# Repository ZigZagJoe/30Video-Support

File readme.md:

This is the support repository for the 30Video series of video cards, by zigzagjoe.

https://68kmla.org/bb/index.php?threads/fs-30video-gs-internal-grayscale-for-se-30.47879/
https://68kmla.org/bb/index.php?threads/30video-new-video-board-for-se-30-iisi-more.47649/

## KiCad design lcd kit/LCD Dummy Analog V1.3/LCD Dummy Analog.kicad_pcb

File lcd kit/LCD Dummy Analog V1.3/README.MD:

# LCD Kit "Analog" Board.
This board is used to replace the original analog board.

The contents of this folder are subject to the CERN OHL License, the contents of which follow.

Please do not commercially distribute these boards without first contacting me. Selling extra boards in a noncommercial fashion not for profit is fine. 

# CERN Open Hardware Licence Version 2 - Strongly Reciprocal

Preamble

CERN has developed this licence to promote collaboration among
hardware designers and to provide a legal tool which supports the
freedom to use, study, modify, share and distribute hardware designs
and products based on those designs. Version 2 of the CERN Open
Hardware Licence comes in three variants: CERN-OHL-P (permissive); and
two reciprocal licences: CERN-OHL-W (weakly reciprocal) and this
licence, CERN-OHL-S (strongly reciprocal).

The CERN-OHL-S is copyright CERN 2020. Anyone is welcome to use it, in
unmodified form only.

Use of this Licence does not imply any endorsement by CERN of any
Licensor or their designs nor does it imply any involvement by CERN in
their development.

1 Definitions

  1.1 'Licence' means this CERN-OHL-S.

  1.2 'Compatible Licence' means

       a) any earlier version of the CERN Open Hardware licence, or

       b) any version of the CERN-OHL-S, or

       c) any licence which permits You to treat the Source to which
          it applies as licensed under CERN-OHL-S provided that on
          Conveyance of any such Source, or any associated Product You
          treat the Source in question as being licensed under
          CERN-OHL-S.

  1.3 'Source' means information such as design materials or digital
      code which can be applied to Make or test a Product or to
      prepare a Product for use, Conveyance or sale, regardless of its
      medium or how it is expressed. It may include Notices.

  1.4 'Covered Source' means Source that is explicitly made available
      under this Licence.

  1.5 'Product' means any device, component, work or physical object,
      whether in finished or intermediate form, arising from the use,
      application or processing of Covered Source.

  1.6 'Make' means to create or configure something, whether by
      manufacture, assembly, compiling, loading or applying Covered
      Source or another Product or otherwise.

  1.7 'Available Component' means any part, sub-assembly, library or
      code which:

       a) is licensed to You as Complete Source under a Compatible
          Licence; or

       b) is available, at the time a Product or the Source containing
          it is first Conveyed, to You and any other prospective
          licensees

            i) as a physical part with sufficient rights and
               information (including any configuration and
               programming files and information about its
               characteristics and interfaces) to enable it either to
               be Made itself, or to be sourced and used to Make the
               Product; or
           ii) as part of the normal distribution of a tool used to
               design or Make the Product.

  1.8 'Complete Source' means the set of all Source necessary to Make
      a Product, in the preferred form for making modifications,
      including necessary installation and interfacing information
      both for the Product, and for any included Available Components.
      If the format is proprietary, it must also be made available in
      a format (if the proprietary tool can create it) which is
      viewable with a tool available to potential licensees and
      licensed under a licence approved by the Free Software
      Foundation or the Open Source Initiative. Complete Source need
      not include the Source of any Available Component, provided that
      You include in the Complete Source sufficient information to
      enable a recipient to Make or source and use the Available
      Component to Make the Product.

  1.9 'Source Location' means a location where a Licensor has placed
      Covered Source, and which that Licensor reasonably believes will
      remain easily accessible for at least three years for anyone to
      obtain a digital copy.

 1.10 'Notice' means copyright, acknowledgement and trademark notices,
      Source Location references, modification notices (subsection
      3.3(b)) and all notices that refer to this Licence and to the
      disclaimer of warranties that are included in the Covered
      Source.

 1.11 'Licensee' or 'You' means any person exercising rights under
      this Licence.

 1.12 'Licensor' means a natural or legal person who creates or
      modifies Covered Source. A person may be a Licensee and a
      Licensor at the same time.

 1.13 'Convey' means to communicate to the public or distribute.

2 Applicability

  2.1 This Licence governs the use, copying, modification, Conveying
      of Covered Source and Products, and the Making of Products. By
      exercising any right granted under this Licence, You irrevocably
      accept these terms and conditions.

  2.2 This Licence is granted by the Licensor directly to You, and
      shall apply worldwide and without limitation in time.

  2.3 You shall not attempt to restrict by contract or otherwise the
      rights granted under this Licence to other Licensees.

  2.4 This Licence is not intended to restrict fair use, fair dealing,
      or any other similar right.

3 Copying, Modifying and Conveying Covered Source

  3.1 You may copy and Convey verbatim copies of Covered Source, in
      any medium, provided You retain all Notices.

  3.2 You may modify Covered Source, other than Notices, provided that
      You irrevocably undertake to make that modified Covered Source
      available from a Source Location should You Convey a Product in
      circumstances where the recipient does not otherwise receive a
      copy of the modified Covered Source. In each case subsection 3.3
      shall apply.

      You may only delete Notices if they are no longer applicable to
      the corresponding Covered Source as modified by You and You may
      add additional Notices applicable to Your modifications.
      Including Covered Source in a larger work is modifying the
      Covered Source, and the larger work becomes modified Covered
      Source.

  3.3 You may Convey modified Covered Source (with the effect that You
      shall also become a Licensor) provided that You:

       a) retain Notices as required in subsection 3.2;

       b) add a Notice to the modified Covered Source stating that You
          have modified it, with the date and brief description of how
          You have modified it;

       c) add a Source Location Notice for the modified Covered Source
          if You Convey in circumstances where the recipient does not
          otherwise receive a copy of the modified Covered Source; and

       d) license the modified Covered Source under the terms and
          conditions of this Licence (or, as set out in subsection
          8.3, a later version, if permitted by the licence of the
          original Covered Source). Such modified Covered Source must
          be licensed as a whole, but excluding Available Components
          contained in it, which remain licensed under their own
          applicable licences.

4 Making and Conveying Products

You may Make Products, and/or Convey them, provided that You either
provide each recipient with a copy of the Complete Source or ensure
that each recipient is notified of the Source Location of the Complete
Source. That Complete Source is Covered Source, and You must
accordingly satisfy Your obligations set out in subsection 3.3. If
specified in a Notice, the Product must visibly and securely display
the Source Location on it or its packaging or documentation in the
manner specified in that Notice.

5 Research and Development

You may Convey Covered Source, modified Covered Source or Products to
a legal entity carrying out development, testing or quality assurance
work on Your behalf provided that the work is performed on terms which
prevent the entity from both using the Source or Products for its own
internal purposes and Conveying the Source or Products or any
modifications to them to any person other than You. Any modifications
made by the entity shall be deemed to be made by You pursuant to
subsection 3.2.

6 DISCLAIMER AND LIABILITY

  6.1 DISCLAIMER OF WARRANTY -- The Covered Source and any Products
      are provided 'as is' and any express or implied warranties,
      including, but not limited to, implied warranties of
      merchantability, of satisfactory quality, non-infringement of
      third party rights, and fitness for a particular purpose or use
      are disclaimed in respect of any Source or Product to the
      maximum extent permitted by law. The Licensor makes no
      representation that any Source or Product does not or will not
      infringe any patent, copyright, trade secret or other
      proprietary right. The entire risk as to the use, quality, and
      performance of any Source or Product shall be with You and not
      the Licensor. This disclaimer of warranty is an essential part
      of this Licence and a condition for the grant of any rights
      granted under this Licence.

  6.2 EXCLUSION AND LIMITATION OF LIABILITY -- The Licensor shall, to
      the maximum extent permitted by law, have no liability for
      direct, indirect, special, incidental, consequential, exemplary,
      punitive or other damages of any character including, without
      limitation, procurement of substitute goods or services, loss of
      use, data or profits, or business interruption, however caused
      and on any theory of contract, warranty, tort (including
      negligence), product liability or otherwise, arising in any way
      in relation to the Covered Source, modified Covered Source
      and/or the Making or Conveyance of a Product, even if advised of
      the possibility of such damages, and You shall hold the
      Licensor(s) free and harmless from any liability, costs,
      damages, fees and expenses, including claims by third parties,
      in relation to such use.

7 Patents

  7.1 Subject to the terms and conditions of this Licence, each
      Licensor hereby grants to You a perpetual, worldwide,
      non-exclusive, no-charge, royalty-free, irrevocable (except as
      stated in subsections 7.2 and 8.4) patent licence to Make, have
      Made, use, offer to sell, sell, import, and otherwise transfer
      the Covered Source and Products, where such licence applies only
      to those patent claims licensable by such Licensor that are
      necessarily infringed by exercising rights under the Covered
      Source as Conveyed by that Licensor.

  7.2 If You institute patent litigation against any entity (including
      a cross-claim or counterclaim in a lawsuit) alleging that the
      Covered Source or a Product constitutes direct or contributory
      patent infringement, or You seek any declaration that a patent
      licensed to You under this Licence is invalid or unenforceable
      then any rights granted to You under this Licence shall
      terminate as of the date such process is initiated.

8 General

  8.1 If any provisions of this Licence are or subsequently become
      invalid or unenforceable for any reason, the remaining
      provisions shall remain effective.

  8.2 You shall not use any of the name (including acronyms and
      abbreviations), image, or logo by which the Licensor or CERN is
      known, except where needed to comply with section 3, or where
      the use is otherwise allowed by law. Any such permitted use
      shall be factual and shall not be made so as to suggest any kind
      of endorsement or implication of involvement by the Licensor or
      its personnel.

  8.3 CERN may publish updated versions and variants of this Licence
      which it considers to be in the spirit of this version, but may
      differ in detail to address new problems or concerns. New
      versions will be published with a unique version number and a
      variant identifier specifying the variant. If the Licensor has
      specified that a given variant applies to the Covered Source
      without specifying a version, You may treat that Covered Source
      as being released under any version of the CERN-OHL with that
      variant. If no variant is specified, the Covered Source shall be
      treated as being released under CERN-OHL-S. The Licensor may
      also specify that the Covered Source is subject to a specific
      version of the CERN-OHL or any later version in which case You
      may apply this or any later version of CERN-OHL with the same
      variant identifier published by CERN.

  8.4 This Licence shall terminate with immediate effect if You fail
      to comply with any of its terms and conditions.

  8.5 However, if You cease all breaches of this Licence, then Your
      Licence from any Licensor is reinstated unless such Licensor has
      terminated this Licence by giving You, while You remain in
      breach, a notice specifying the breach and requiring You to cure
      it within 30 days, and You have failed to come into compliance
      in all material respects by the end of the 30 day period. Should
      You repeat the breach after receipt of a cure notice and
      subsequent reinstatement, this Licence will terminate
      immediately and permanently. Section 6 shall continue to apply
      after any termination.

  8.6 This Licence shall not be enforceable except by a Licensor
      acting as such, and third party beneficiary rights are
      specifically excluded.

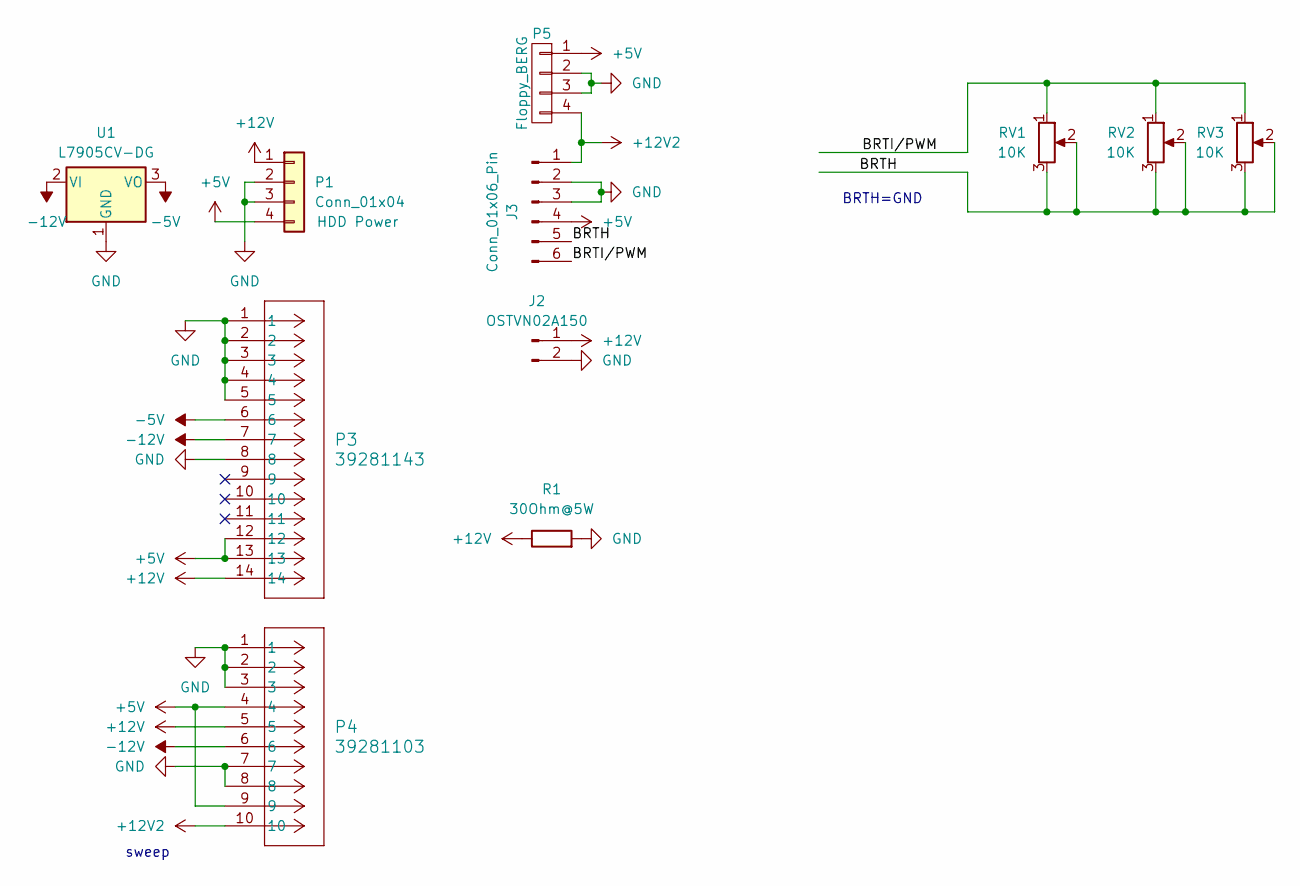
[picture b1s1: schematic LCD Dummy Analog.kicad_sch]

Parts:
J2: OSTVN02A150; PinHeader_1x02_P2.54mm_Vertical
J3: Conn_01x06_Pin; JST_XH_B6B-XH-A_1x06_P2.50mm_Vertical
P1: Conn_01x04; TE_MATE-N-LOK_350211-1_1x04_P5.08mm_Vertical
P3: 39281143; SE30AB_CON_39281143
P4: 39281103; SE30AB_CON_39281103
P5: Floppy_BERG; floppy-berg; digikey S9490-ND
R1: 30Ohm@5W; R_Axial_Power_L25.0mm_W6.4mm_P30.48mm
RV1, RV2, RV3: 10K; Potentiometer_Piher_T-16H_Single_Horizontal
U1: L7905CV-DG; TO-220-3_Horizontal_TabDown

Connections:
+5V: J3.4, P1.4, P3.12, P3.13, P4.4, P4.9, P5.1
+12V: J2.1, P1.1, P3.14, P4.5, R1.1
+12V2: J3.1, P4.10, P5.4
-5V: P3.6, U1.3 (VO)
-12V: P3.7, P4.6, U1.2 (VI)
/BRTH: J3.5, RV1.2, RV1.3, RV2.2, RV2.3, RV3.2, RV3.3
/BRTI/PWM: J3.6, RV1.1, RV2.1, RV3.1
GND: J2.2, J3.2, J3.3, P1.2, P1.3, P3.1, P3.2, P3.3, P3.4, P3.5, P3.8, P4.1, P4.2, P4.3, P4.7, P4.8, P5.2, P5.3, R1.2, U1.1 (GND)

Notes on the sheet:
sweep
BRTH=GND

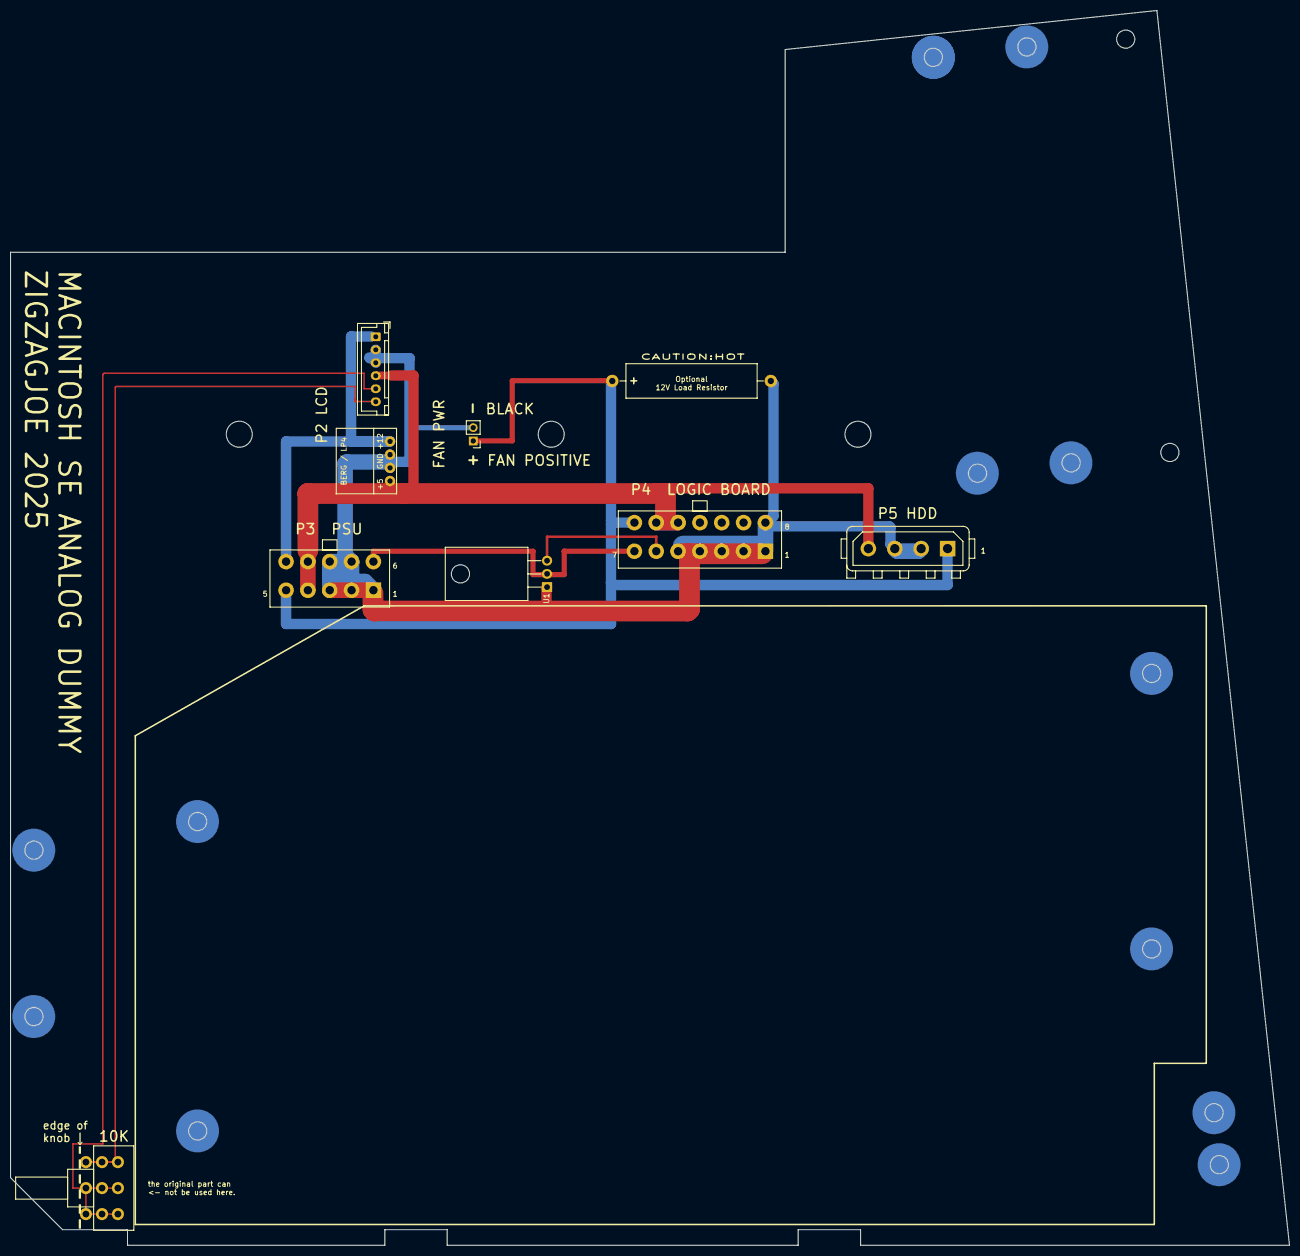
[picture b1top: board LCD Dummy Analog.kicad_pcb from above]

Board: 2 copper layers, 246.0 x 237.5 mm, 11 parts (0 on the bottom side), 8 nets.

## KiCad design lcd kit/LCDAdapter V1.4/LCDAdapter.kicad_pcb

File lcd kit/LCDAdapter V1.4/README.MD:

# LCD Kit "Adapter" Board
This board is used to adapt the 30Video's LCD interface to the NL6448BC26-26F.

The contents of this folder are subject to the CERN OHL License, the contents of which follow.

Please do not commercially distribute these boards without first contacting me. Selling extra boards in a noncommercial fashion not for profit is fine. 

# CERN Open Hardware Licence Version 2 - Strongly Reciprocal

Preamble

CERN has developed this licence to promote collaboration among
hardware designers and to provide a legal tool which supports the
freedom to use, study, modify, share and distribute hardware designs
and products based on those designs. Version 2 of the CERN Open
Hardware Licence comes in three variants: CERN-OHL-P (permissive); and
two reciprocal licences: CERN-OHL-W (weakly reciprocal) and this
licence, CERN-OHL-S (strongly reciprocal).

The CERN-OHL-S is copyright CERN 2020. Anyone is welcome to use it, in
unmodified form only.

Use of this Licence does not imply any endorsement by CERN of any
Licensor or their designs nor does it imply any involvement by CERN in
their development.

1 Definitions

  1.1 'Licence' means this CERN-OHL-S.

  1.2 'Compatible Licence' means

       a) any earlier version of the CERN Open Hardware licence, or

       b) any version of the CERN-OHL-S, or

       c) any licence which permits You to treat the Source to which
          it applies as licensed under CERN-OHL-S provided that on
          Conveyance of any such Source, or any associated Product You
          treat the Source in question as being licensed under
          CERN-OHL-S.

  1.3 'Source' means information such as design materials or digital
      code which can be applied to Make or test a Product or to
      prepare a Product for use, Conveyance or sale, regardless of its
      medium or how it is expressed. It may include Notices.

  1.4 'Covered Source' means Source that is explicitly made available
      under this Licence.

  1.5 'Product' means any device, component, work or physical object,
      whether in finished or intermediate form, arising from the use,
      application or processing of Covered Source.

  1.6 'Make' means to create or configure something, whether by
      manufacture, assembly, compiling, loading or applying Covered
      Source or another Product or otherwise.

  1.7 'Available Component' means any part, sub-assembly, library or
      code which:

       a) is licensed to You as Complete Source under a Compatible
          Licence; or

       b) is available, at the time a Product or the Source containing
          it is first Conveyed, to You and any other prospective
          licensees

            i) as a physical part with sufficient rights and
               information (including any configuration and
               programming files and information about its
               characteristics and interfaces) to enable it either to
               be Made itself, or to be sourced and used to Make the
               Product; or
           ii) as part of the normal distribution of a tool used to
               design or Make the Product.

  1.8 'Complete Source' means the set of all Source necessary to Make
      a Product, in the preferred form for making modifications,
      including necessary installation and interfacing information
      both for the Product, and for any included Available Components.
      If the format is proprietary, it must also be made available in
      a format (if the proprietary tool can create it) which is
      viewable with a tool available to potential licensees and
      licensed under a licence approved by the Free Software
      Foundation or the Open Source Initiative. Complete Source need
      not include the Source of any Available Component, provided that
      You include in the Complete Source sufficient information to
      enable a recipient to Make or source and use the Available
      Component to Make the Product.

  1.9 'Source Location' means a location where a Licensor has placed
      Covered Source, and which that Licensor reasonably believes will
      remain easily accessible for at least three years for anyone to
      obtain a digital copy.

 1.10 'Notice' means copyright, acknowledgement and trademark notices,
      Source Location references, modification notices (subsection
      3.3(b)) and all notices that refer to this Licence and to the
      disclaimer of warranties that are included in the Covered
      Source.

 1.11 'Licensee' or 'You' means any person exercising rights under
      this Licence.

 1.12 'Licensor' means a natural or legal person who creates or
      modifies Covered Source. A person may be a Licensee and a
      Licensor at the same time.

 1.13 'Convey' means to communicate to the public or distribute.

2 Applicability

  2.1 This Licence governs the use, copying, modification, Conveying
      of Covered Source and Products, and the Making of Products. By
      exercising any right granted under this Licence, You irrevocably
      accept these terms and conditions.

  2.2 This Licence is granted by the Licensor directly to You, and
      shall apply worldwide and without limitation in time.

  2.3 You shall not attempt to restrict by contract or otherwise the
      rights granted under this Licence to other Licensees.

  2.4 This Licence is not intended to restrict fair use, fair dealing,
      or any other similar right.

3 Copying, Modifying and Conveying Covered Source

  3.1 You may copy and Convey verbatim copies of Covered Source, in
      any medium, provided You retain all Notices.

  3.2 You may modify Covered Source, other than Notices, provided that
      You irrevocably undertake to make that modified Covered Source
      available from a Source Location should You Convey a Product in
      circumstances where the recipient does not otherwise receive a
      copy of the modified Covered Source. In each case subsection 3.3
      shall apply.

      You may only delete Notices if they are no longer applicable to
      the corresponding Covered Source as modified by You and You may
      add additional Notices applicable to Your modifications.
      Including Covered Source in a larger work is modifying the
      Covered Source, and the larger work becomes modified Covered
      Source.

  3.3 You may Convey modified Covered Source (with the effect that You
      shall also become a Licensor) provided that You:

       a) retain Notices as required in subsection 3.2;

       b) add a Notice to the modified Covered Source stating that You
          have modified it, with the date and brief description of how
          You have modified it;

       c) add a Source Location Notice for the modified Covered Source
          if You Convey in circumstances where the recipient does not
          otherwise receive a copy of the modified Covered Source; and

       d) license the modified Covered Source under the terms and
          conditions of this Licence (or, as set out in subsection
          8.3, a later version, if permitted by the licence of the
          original Covered Source). Such modified Covered Source must
          be licensed as a whole, but excluding Available Components
          contained in it, which remain licensed under their own
          applicable licences.

4 Making and Conveying Products

You may Make Products, and/or Convey them, provided that You either
provide each recipient with a copy of the Complete Source or ensure
that each recipient is notified of the Source Location of the Complete
Source. That Complete Source is Covered Source, and You must
accordingly satisfy Your obligations set out in subsection 3.3. If
specified in a Notice, the Product must visibly and securely display
the Source Location on it or its packaging or documentation in the
manner specified in that Notice.

5 Research and Development

You may Convey Covered Source, modified Covered Source or Products to
a legal entity carrying out development, testing or quality assurance
work on Your behalf provided that the work is performed on terms which
prevent the entity from both using the Source or Products for its own
internal purposes and Conveying the Source or Products or any
modifications to them to any person other than You. Any modifications
made by the entity shall be deemed to be made by You pursuant to
subsection 3.2.

6 DISCLAIMER AND LIABILITY

  6.1 DISCLAIMER OF WARRANTY -- The Covered Source and any Products
      are provided 'as is' and any express or implied warranties,
      including, but not limited to, implied warranties of
      merchantability, of satisfactory quality, non-infringement of
      third party rights, and fitness for a particular purpose or use
      are disclaimed in respect of any Source or Product to the
      maximum extent permitted by law. The Licensor makes no
      representation that any Source or Product does not or will not
      infringe any patent, copyright, trade secret or other
      proprietary right. The entire risk as to the use, quality, and
      performance of any Source or Product shall be with You and not
      the Licensor. This disclaimer of warranty is an essential part
      of this Licence and a condition for the grant of any rights
      granted under this Licence.

  6.2 EXCLUSION AND LIMITATION OF LIABILITY -- The Licensor shall, to
      the maximum extent permitted by law, have no liability for
      direct, indirect, special, incidental, consequential, exemplary,
      punitive or other damages of any character including, without
      limitation, procurement of substitute goods or services, loss of
      use, data or profits, or business interruption, however caused
      and on any theory of contract, warranty, tort (including
      negligence), product liability or otherwise, arising in any way
      in relation to the Covered Source, modified Covered Source
      and/or the Making or Conveyance of a Product, even if advised of
      the possibility of such damages, and You shall hold the
      Licensor(s) free and harmless from any liability, costs,
      damages, fees and expenses, including claims by third parties,
      in relation to such use.

7 Patents

  7.1 Subject to the terms and conditions of this Licence, each
      Licensor hereby grants to You a perpetual, worldwide,
      non-exclusive, no-charge, royalty-free, irrevocable (except as
      stated in subsections 7.2 and 8.4) patent licence to Make, have
      Made, use, offer to sell, sell, import, and otherwise transfer
      the Covered Source and Products, where such licence applies only
      to those patent claims licensable by such Licensor that are
      necessarily infringed by exercising rights under the Covered
      Source as Conveyed by that Licensor.

  7.2 If You institute patent litigation against any entity (including
      a cross-claim or counterclaim in a lawsuit) alleging that the
      Covered Source or a Product constitutes direct or contributory
      patent infringement, or You seek any declaration that a patent
      licensed to You under this Licence is invalid or unenforceable
      then any rights granted to You under this Licence shall
      terminate as of the date such process is initiated.

8 General

  8.1 If any provisions of this Licence are or subsequently become
      invalid or unenforceable for any reason, the remaining
      provisions shall remain effective.

  8.2 You shall not use any of the name (including acronyms and
      abbreviations), image, or logo by which the Licensor or CERN is
      known, except where needed to comply with section 3, or where
      the use is otherwise allowed by law. Any such permitted use
      shall be factual and shall not be made so as to suggest any kind
      of endorsement or implication of involvement by the Licensor or
      its personnel.

  8.3 CERN may publish updated versions and variants of this Licence
      which it considers to be in the spirit of this version, but may
      differ in detail to address new problems or concerns. New
      versions will be published with a unique version number and a
      variant identifier specifying the variant. If the Licensor has
      specified that a given variant applies to the Covered Source
      without specifying a version, You may treat that Covered Source
      as being released under any version of the CERN-OHL with that
      variant. If no variant is specified, the Covered Source shall be
      treated as being released under CERN-OHL-S. The Licensor may
      also specify that the Covered Source is subject to a specific
      version of the CERN-OHL or any later version in which case You
      may apply this or any later version of CERN-OHL with the same
      variant identifier published by CERN.

  8.4 This Licence shall terminate with immediate effect if You fail
      to comply with any of its terms and conditions.

  8.5 However, if You cease all breaches of this Licence, then Your
      Licence from any Licensor is reinstated unless such Licensor has
      terminated this Licence by giving You, while You remain in
      breach, a notice specifying the breach and requiring You to cure
      it within 30 days, and You have failed to come into compliance
      in all material respects by the end of the 30 day period. Should
      You repeat the breach after receipt of a cure notice and
      subsequent reinstatement, this Licence will terminate
      immediately and permanently. Section 6 shall continue to apply
      after any termination.

  8.6 This Licence shall not be enforceable except by a Licensor
      acting as such, and third party beneficiary rights are
      specifically excluded.

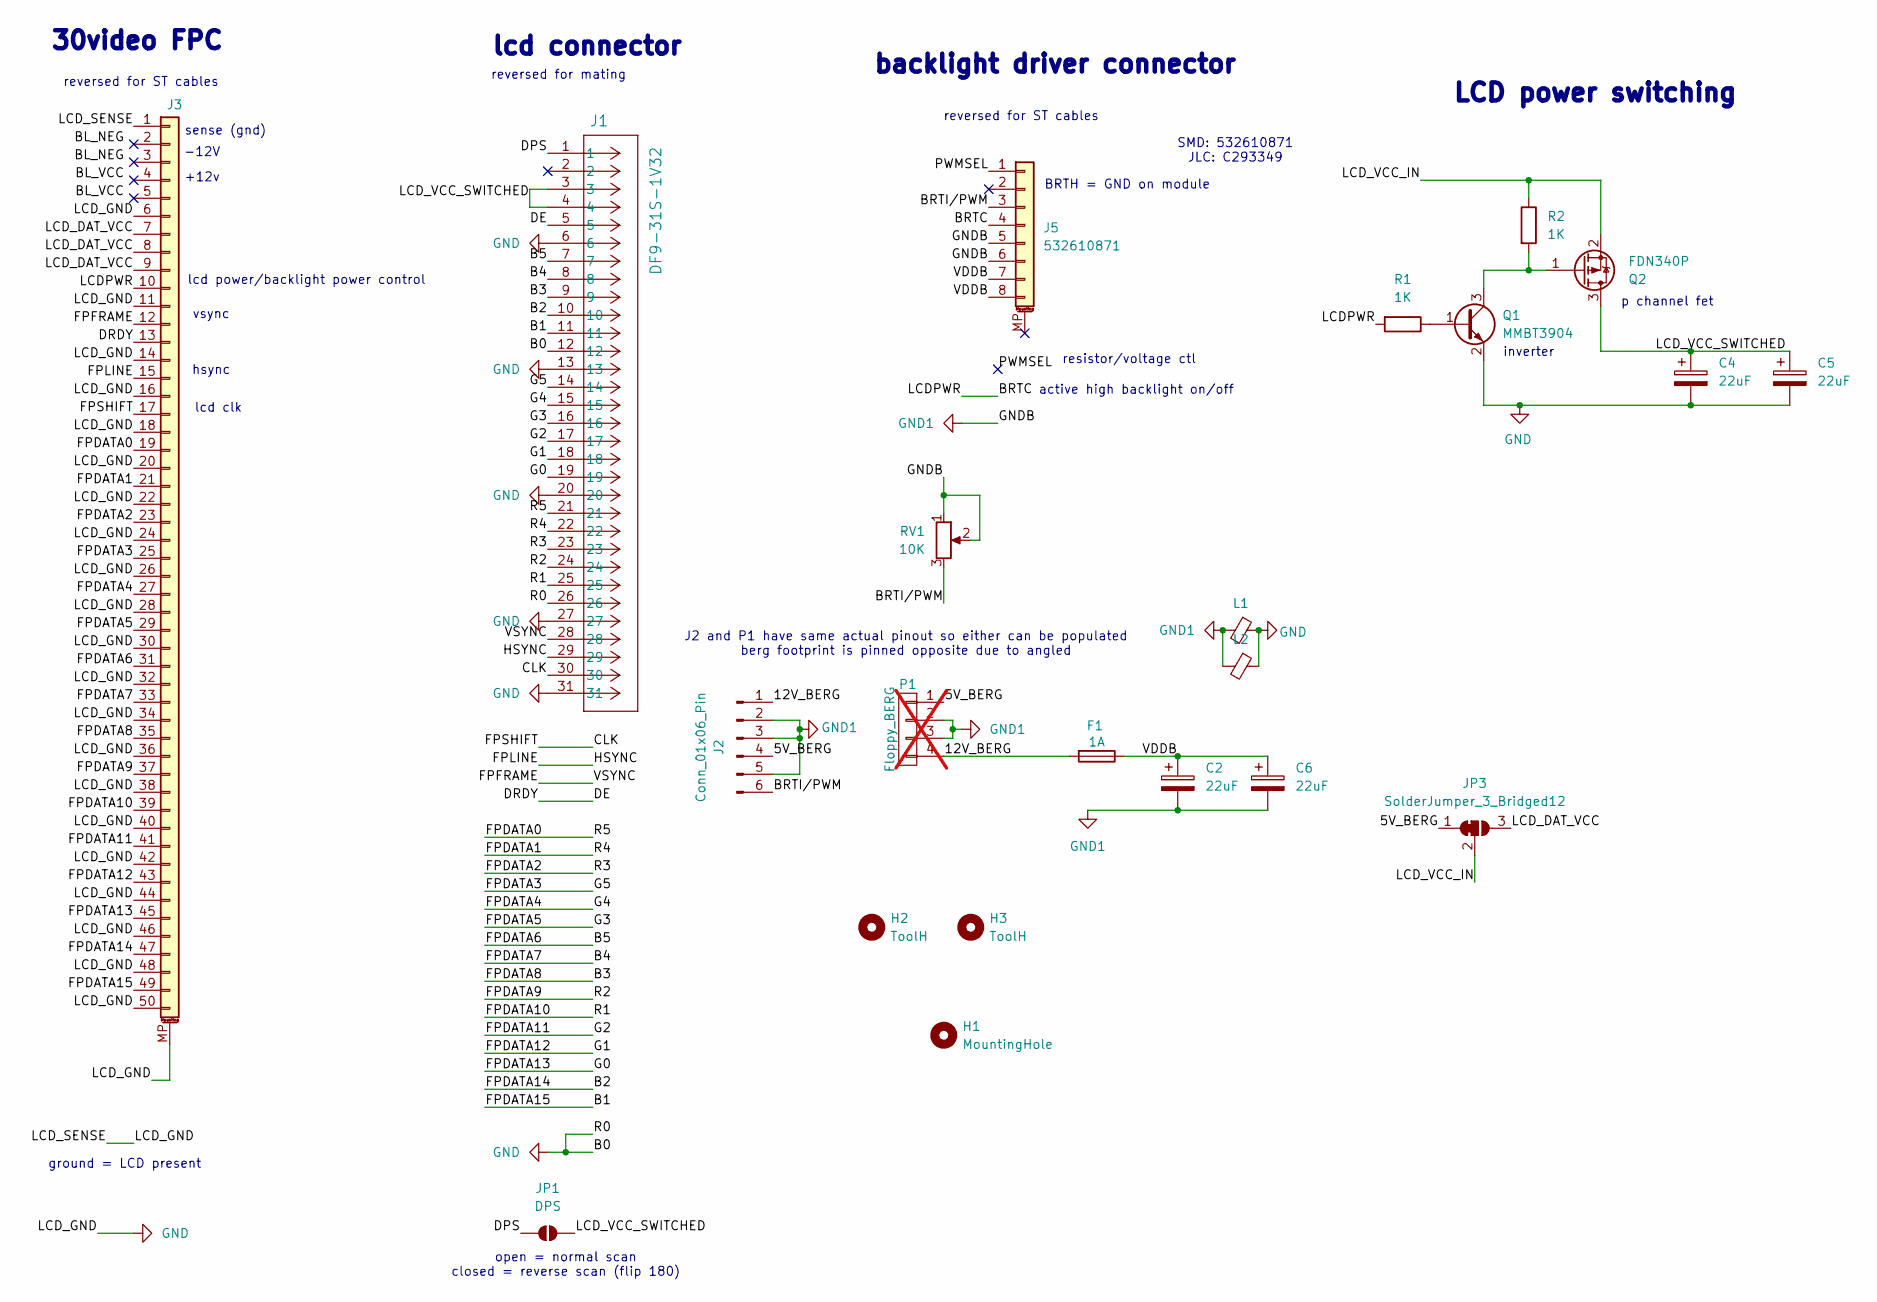
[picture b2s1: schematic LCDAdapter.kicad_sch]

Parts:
C2, C4, C5, C6: 22uF; R_0805_2012Metric_HandSolder_XL; PartNumber CL21A226MAQNNNE; LCSC C45783
F1: 1A; Fuse_1206_3216Metric_Pad1.42x1.75mm_HandSolder; LCSC C70082
H1: MountingHole; MountingHole_4mm; digikey n/a
H2, H3: ToolH; JLC_ToolHole
J1: DF9-31S-1V32; Hirose DF9-31S-1V32; digikey DF9-31S-1V32
J2: Conn_01x06_Pin; Hybrid BergJST-XH-6 + Brightness
J3: Conn_01x50_MountingPin; Molex 541325097_Handsolder; LCSC C11063
J5: 532610871; Molex 532610871; LCSC C293349
JP1: DPS; SolderJumper-2-Open 1MM; digikey na
JP3: SolderJumper_3_Bridged12; SolderJumper-3_P1.3mm_Bridged12_RoundedPad1.0x1.5mm
L1, L2: 600Ω@100MHz; L_0805_2012Metric_Pad1.15x1.40mm_HandSolder; PartNumber GZ2012D601TF; LCSC C1017
P1: Floppy_BERG; floppy-berg; digikey S9490-ND; not fitted
Q1: MMBT3904; SOT-23_Handsoldering; PartNumber MMBT3904; LCSC C20526
Q2: FDN340P; SOT-23_Handsoldering; digikey FDN340PCT-ND
R1, R2: 1K; R_0603_1608Metric; LCSC C21190
RV1: 10K; Bourns 3306F1103; Mouser 3306F-1-103

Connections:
/5V_BERG: J2.4, JP3.1 (A), P1.1
/12V_BERG: F1.2, J2.1, P1.4
/B1: J1.11, J3.49
/B2: J1.10, J3.47
/B3: J1.9, J3.35
/B4: J1.8, J3.33
/B5: J1.7, J3.31
/BRTC: J3.10, J5.4, R1.2
/BRTI/PWM: J2.6, J5.3, RV1.3
/CLK: J1.30, J3.17
/DE: J1.5, J3.13
/DPS: J1.1, JP1.1 (A)
/FPDATA0: J1.21, J3.19
/FPDATA1: J1.22, J3.21
/FPDATA2: J1.23, J3.23
/FPDATA3: J1.14, J3.25
/FPDATA4: J1.15, J3.27
/FPDATA5: J1.16, J3.29
/FPDATA9: J1.24, J3.37
/FPDATA10: J1.25, J3.39
/FPDATA11: J1.17, J3.41
/FPDATA12: J1.18, J3.43
/FPDATA13: J1.19, J3.45
/FPFRAME: J1.28, J3.12
/FPLINE: J1.29, J3.15
/LCD_DAT_VCC: J3.7, J3.8, J3.9, JP3.3 (B)
/LCD_VCC_IN: JP3.2 (C), Q2.2 (S), R2.1
/LCD_VCC_SWITCHED: C4.1, C5.1, J1.3, J1.4, JP1.2 (B), Q2.3 (D)
/PWMSEL: J5.1
/VDDB: C2.1, C6.1, F1.1, J5.7, J5.8
GND: C4.2, C5.2, J1.6, J1.12, J1.13, J1.20, J1.26, J1.27, J1.31, J3.1, J3.6, J3.11, J3.14, J3.16, J3.18, J3.20, J3.22, J3.24, J3.26, J3.28, J3.30, J3.32, J3.34, J3.36, J3.38, J3.40, J3.42, J3.44, J3.46, J3.48, J3.50, J3.MP (MountPin), L1.1, L2.1, Q1.2 (E)
GND1: C2.2, C6.2, J2.2, J2.3, J2.5, J5.5, J5.6, L1.2, L2.2, P1.2, P1.3, RV1.1, RV1.2
unnamed: Q1.1 (B), R1.1
unnamed: Q1.3 (C), Q2.1 (G), R2.2

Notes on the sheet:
30video FPC
resistor/voltage ctl
vsync
lcd connector
lcd clk
open = normal scan closed = reverse scan (flip 180)
-12V
hsync
inverter
LCD power switching
+12v
ground = LCD present
reversed for ST cables
sense (gnd)
p channel fet
J2 and P1 have same actual pinout so either can be populated berg footprint is pinned opposite due to angled
SMD: 532610871 JLC: C293349
BRTH = GND on module
lcd power/backlight power control
active high backlight on/off
reversed for mating
backlight driver connector

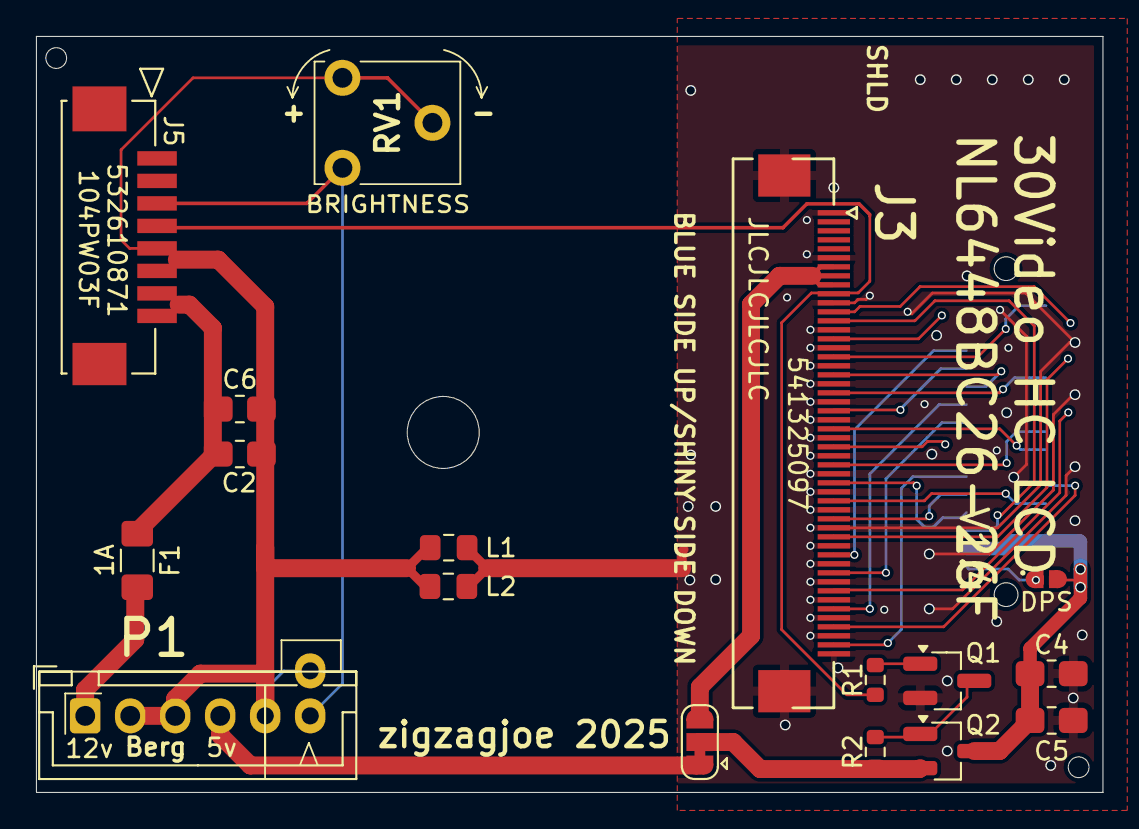
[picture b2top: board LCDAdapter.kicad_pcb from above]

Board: 2 copper layers, 59.2 x 42.0 mm, 21 parts (1 on the bottom side), 33 nets.

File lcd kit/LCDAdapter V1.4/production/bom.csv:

Designator,Footprint,Quantity,Value,LCSC Part #
"C2, C4, C5, C6",0805,4,22uF,C45783
F1,1206,1,1A,C70082
J1,Hirose DF9-31S-1V32,1,DF9-31S-1V32,
J2,Hybrid BergJST-XH-6 + Brightness,1,Conn_01x06_Pin,
J3,Molex 541325097_Handsolder,1,Conn_01x50_MountingPin,C11063
J5,Molex 532610871,1,532610871,C293349
"L1, L2",0805,2,600Ω@100MHz,C1017
Q1,SOT-23_Handsoldering,1,MMBT3904,C20526
Q2,SOT-23_Handsoldering,1,FDN340P,
"R1, R2",0603,2,1K,C21190
RV1,Bourns 3306F1103,1,10K,

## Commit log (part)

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2024-06-28 update doc
2024-07-07 update guide
2024-07-11 update doc:
2024-07-12 update doc, add bolle NBtweak
2024-07-17 add shipping FW
2024-07-17 add harness and NB references
2024-07-17 add readme
2024-07-23 add changelog and 1911 beta
2024-07-31 add beta 1917
2024-07-31 Add firmware recovery, move harness and neckboard into subdirs
2024-08-21 Add SI card files
2024-08-21 changelog
2024-08-24 add additional IO board info, SI instructions, change bolle NB gerber
2024-08-27 xga beta
2024-08-27 add macbinary note
2024-09-03 update si documentation
2024-11-02 Add 2065/67 betas and RC for all cards
2024-11-04 fixed RC
2024-11-06 move obsolete versions
2024-11-21 add howto
2024-11-26 add disassembly supplement
2024-11-27 initial HC docs
2024-11-27 update diy
2024-11-27 update HCinstructions
2024-12-01 HC Release 2122
2025-01-02 new V2 mount HC instructions
2025-01-16 beta 2129, don't disable video
2025-03-30 add LCD bracket files, obsolete release versions of SI and GS firmware
2025-03-30 readme.md for firmware updates:
2025-05-12 HCGS cards

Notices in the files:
lcd kit/LCD Dummy Analog V1.3/README.MD:
licensed to You under this Licence is invalid or unenforceable
then any rights granted to You under this Licence shall
as being released under any version of the CERN-OHL with that
treated as being released under CERN-OHL-S. The Licensor may
version of the CERN-OHL or any later version in which case You
may apply this or any later version of CERN-OHL with the same
